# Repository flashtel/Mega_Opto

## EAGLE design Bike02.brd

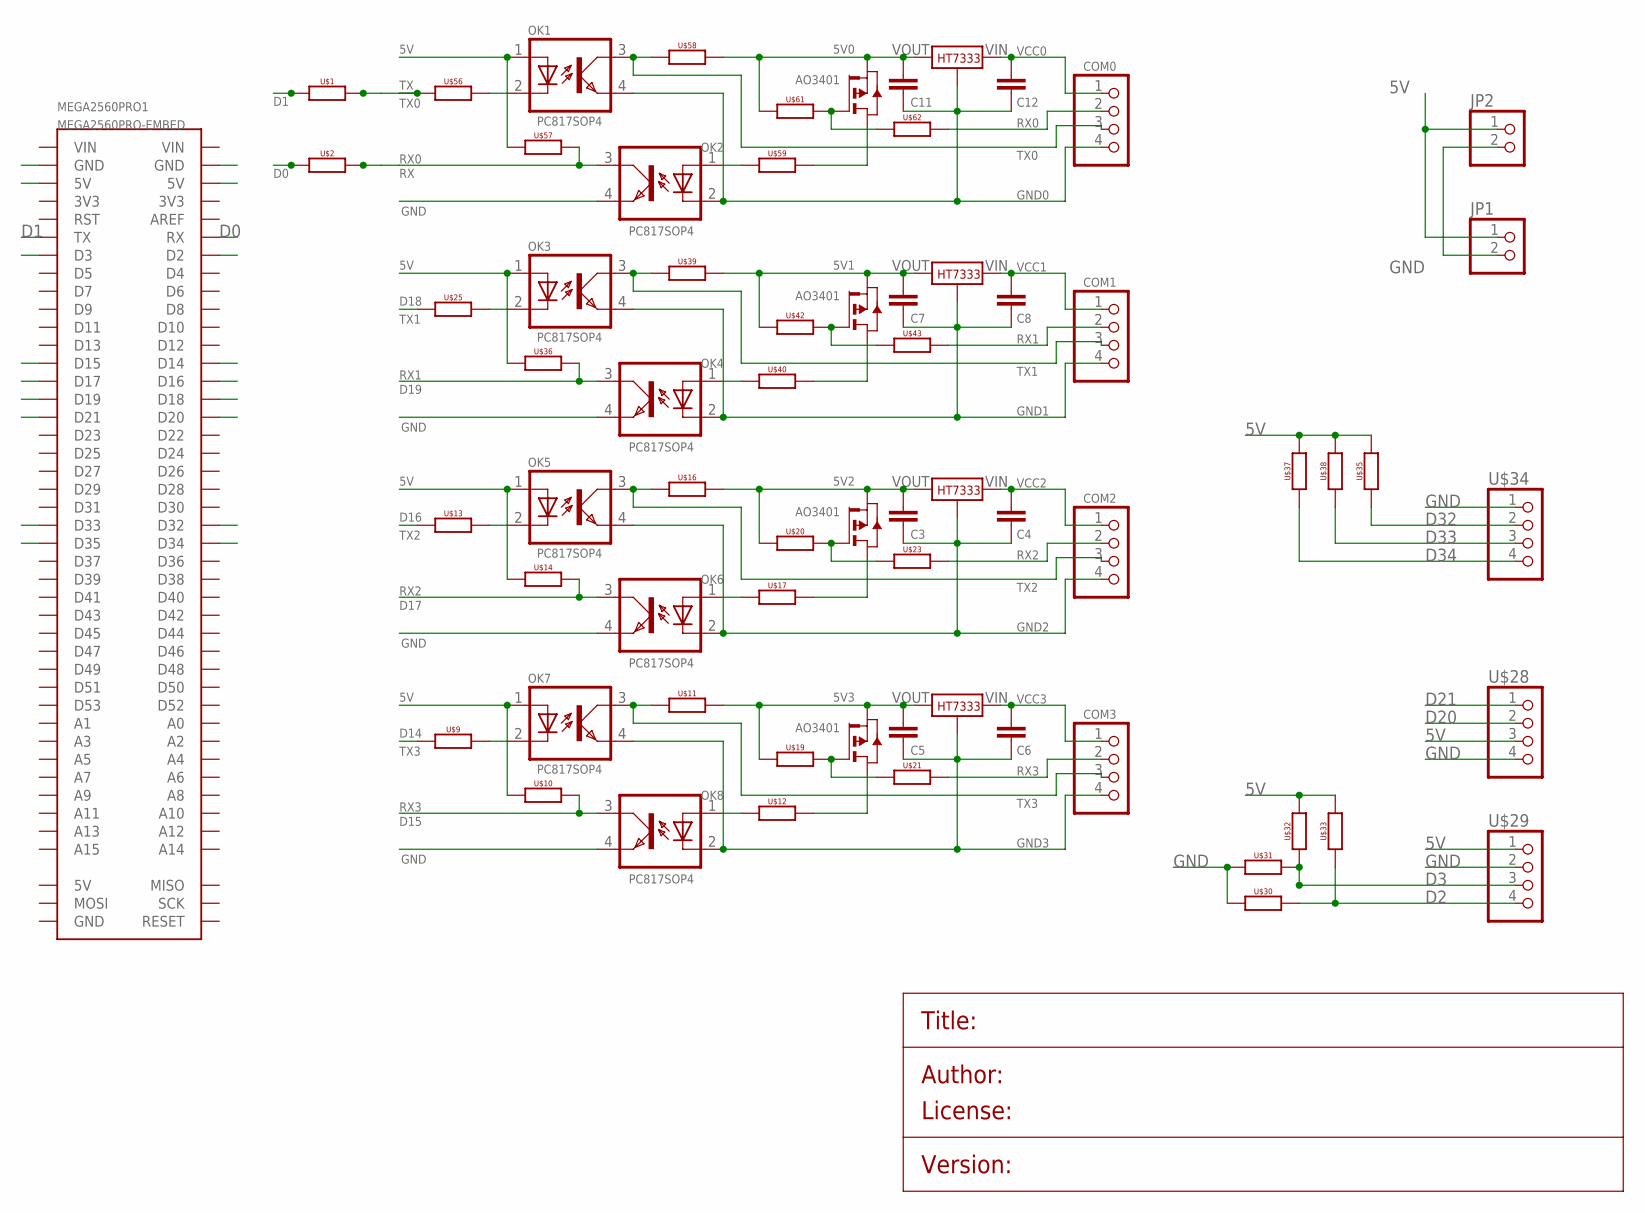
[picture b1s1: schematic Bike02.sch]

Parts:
C3, C4, C5, C6, C7, C8, C11, C12: CAPACITOR0805; 0805
COM0, COM1, COM2, COM3: PINHD-1X4_NO_SILK; 1X04_NO_SILK
JP1, JP2: PINHD-1X2-5_NO_SILK; 1X02-5_NO_SILK
MEGA2560PRO1: MEGA2560PRO-EMBED
OK1, OK2, OK3, OK4, OK5, OK6, OK7, OK8: PC817SOP4; SOP4-2.54
U$1, U$2, U$9, U$10, U$11, U$12, U$13, U$14, U$16, U$17, U$19, U$20, U$21, U$23, U$25, U$30, U$31, U$32, U$33, U$35, U$36, U$37, U$38, U$39, U$40, U$42, U$43, U$56, U$57, U$58, U$59, U$61, U$62: RESISTOR0805; 0805
U$15, U$18, U$41, U$60: AO3401; SOT23
U$22, U$24, U$44, U$63: HT7333; SOT89
U$28, U$29, U$34: PINHD-1X4_NO_SILK; 1X04_NO_SILK

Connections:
5V: JP1.1, JP2.1, MEGA2560PRO1.5V@1 (5V), MEGA2560PRO1.5V@2 (5V), OK1.1 (A), OK3.1 (A), OK5.1 (A), OK7.1 (A), U$10.1, U$14.1, U$28.3, U$29.1, U$32.2, U$33.2, U$35.2, U$36.1, U$37.2, U$38.2, U$57.1
5V0: C11.1, U$58.2, U$60.2 (S), U$61.1, U$63.VOUT
5V1: C7.1, U$39.2, U$41.2 (S), U$42.1, U$44.VOUT
5V2: C3.1, U$16.2, U$18.2 (S), U$20.1, U$24.VOUT
5V3: C5.1, U$11.2, U$15.2 (S), U$19.1, U$22.VOUT
D0: MEGA2560PRO1.RX, U$2.1
D1: MEGA2560PRO1.TX, U$1.1
D2: MEGA2560PRO1.D2, U$29.4, U$30.2, U$33.1
D3: MEGA2560PRO1.D3, U$29.3, U$31.2, U$32.1
D14: MEGA2560PRO1.D14, U$9.1
D15: MEGA2560PRO1.D15, OK8.3 (COL), U$10.2
D16: MEGA2560PRO1.D16, U$13.1
D17: MEGA2560PRO1.D17, OK6.3 (COL), U$14.2
D18: MEGA2560PRO1.D18, U$25.1
D19: MEGA2560PRO1.D19, OK4.3 (COL), U$36.2
D20: MEGA2560PRO1.D20, U$28.2
D21: MEGA2560PRO1.D21, U$28.1
D32: MEGA2560PRO1.D32, U$34.2, U$35.1
D33: MEGA2560PRO1.D33, U$34.3, U$38.1
D34: MEGA2560PRO1.D34, U$34.4, U$37.1
D35: MEGA2560PRO1.D35
GND: JP1.2, JP2.2, MEGA2560PRO1.GND@1 (GND), MEGA2560PRO1.GND@2 (GND), OK2.4 (EMIT), OK4.4 (EMIT), OK6.4 (EMIT), OK8.4 (EMIT), U$28.4, U$29.2, U$30.1, U$31.1, U$34.1
GND0: C11.2, C12.2, COM0.4, OK1.4 (EMIT), OK2.2 (C), U$63.GND
GND1: C7.2, C8.2, COM1.4, OK3.4 (EMIT), OK4.2 (C), U$44.GND
GND2: C3.2, C4.2, COM2.4, OK5.4 (EMIT), OK6.2 (C), U$24.GND
GND3: C5.2, C6.2, COM3.4, OK7.4 (EMIT), OK8.2 (C), U$22.GND
unnamed: OK7.2 (C), U$9.2
unnamed: OK5.2 (C), U$13.2
unnamed: OK6.1 (A), U$17.1
unnamed: OK8.1 (A), U$12.1
unnamed: U$12.2, U$15.3 (D)
unnamed: U$17.2, U$18.3 (D)
unnamed: U$18.1 (G), U$20.2, U$23.1
unnamed: U$15.1 (G), U$19.2, U$21.1
unnamed: OK3.2 (C), U$25.2
unnamed: OK4.1 (A), U$40.1
unnamed: U$40.2, U$41.3 (D)
unnamed: U$41.1 (G), U$42.2, U$43.1
unnamed: OK1.2 (C), U$56.2
unnamed: OK2.1 (A), U$59.1
unnamed: U$59.2, U$60.3 (D)
unnamed: U$60.1 (G), U$61.2, U$62.1
RX: OK2.3 (COL), U$2.2, U$57.2
RX0: COM0.2, U$62.2
RX1: COM1.2, U$43.2
RX2: COM2.2, U$23.2
RX3: COM3.2, U$21.2
TX: U$1.2, U$56.1
TX0: COM0.3, OK1.3 (COL), U$58.1
TX1: COM1.3, OK3.3 (COL), U$39.1
TX2: COM2.3, OK5.3 (COL), U$16.1
TX3: COM3.3, OK7.3 (COL), U$11.1
VCC0: C12.1, COM0.1, U$63.VIN
VCC1: C8.1, COM1.1, U$44.VIN
VCC2: C4.1, COM2.1, U$24.VIN
VCC3: C6.1, COM3.1, U$22.VIN

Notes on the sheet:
TX0
RX0
TX1
RX1
TX2
RX2
TX3
RX3

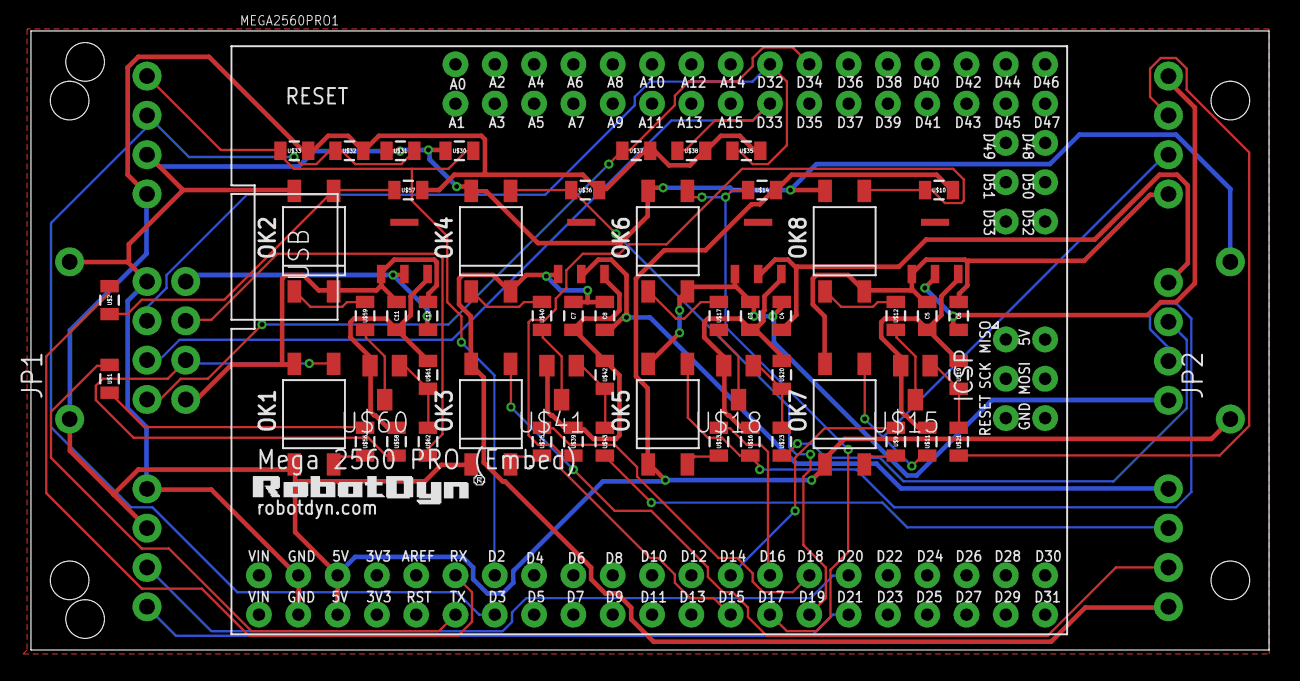
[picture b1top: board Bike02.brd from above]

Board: 2 copper layers, 80.0 x 40.0 mm, 67 parts (0 on the bottom side), 55 nets.

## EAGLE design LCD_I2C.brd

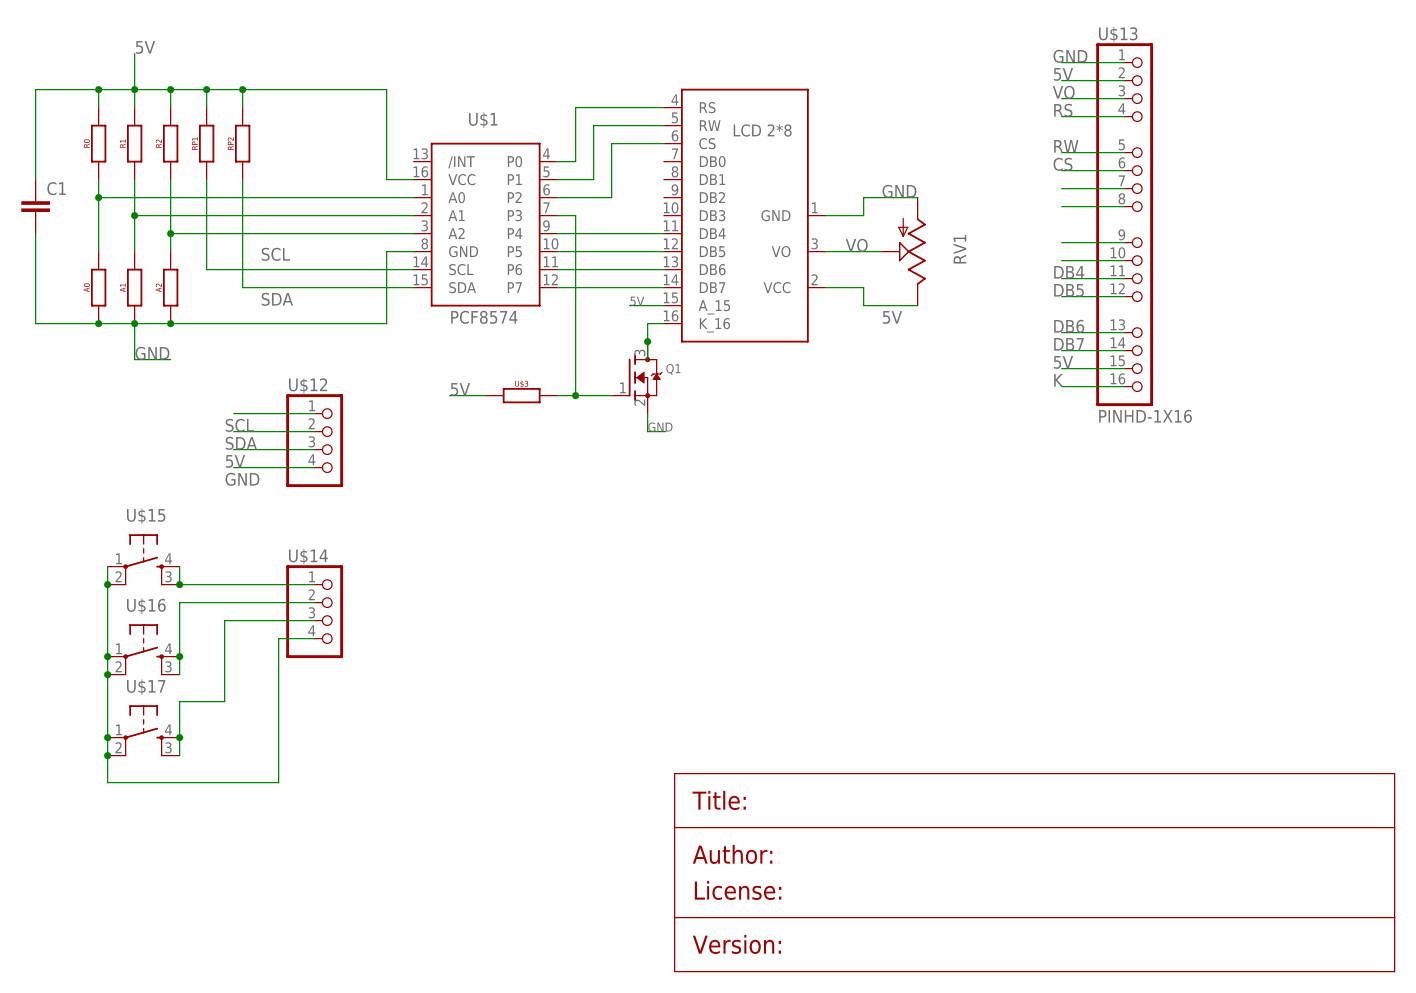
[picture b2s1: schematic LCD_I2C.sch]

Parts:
A0, A1, A2: RESISTOR0805; 0805
C1: CAPACITOR0805; 0805
Q1: MOSFET-N; SOT23-WIDE
R0, R1, R2: RESISTOR0805; 0805
RP1, RP2: RESISTOR0805; 0805
RV1: TRIM_POTB25P; B25P
U$1: PCF8574; SOIC16
U$2: LCD_28_A; LCD_2*8_A
U$3: RESISTOR0805; 0805
U$12, U$14: PINHD-1X4_NO_SILK; 1X04_NO_SILK
U$13: PINHD-1X16; 1X16_NO_SILK
U$15, U$16, U$17: TACTILE_BUTTON_SMD; TACTILE-BUTTON-SMD

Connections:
5V: C1.1, R0.2, R1.2, R2.2, RP1.2, RP2.2, RV1.E, U$1.16 (VCC), U$2.2 (VCC), U$2.15 (A_15), U$3.1, U$12.3, U$13.2, U$13.15
CS: U$1.6 (P2), U$2.6 (CS), U$13.6
DB4: U$1.9 (P4), U$2.11 (DB4), U$13.11
DB5: U$1.10 (P5), U$2.12 (DB5), U$13.12
DB6: U$1.11 (P6), U$2.13 (DB6), U$13.13
DB7: U$1.12 (P7), U$2.14 (DB7), U$13.14
GND: A0.1, A1.1, A2.1, C1.2, Q1.2 (S), RV1.A, U$1.8 (GND), U$2.1 (GND), U$12.4, U$13.1
K: Q1.3 (D), U$2.16 (K_16), U$13.16
unnamed: U$14.4, U$15.1 (SWA1), U$15.2 (SWB1), U$16.1 (SWA1), U$16.2 (SWB1), U$17.1 (SWA1), U$17.2 (SWB1)
unnamed: U$14.1, U$15.3 (SWB2), U$15.4 (SWA2)
unnamed: U$14.2, U$16.3 (SWB2), U$16.4 (SWA2)
unnamed: A0.2, R0.1, U$1.1 (A0)
unnamed: U$14.3, U$17.3 (SWB2), U$17.4 (SWA2)
unnamed: Q1.1 (G), U$1.7 (P3), U$3.2
unnamed: A1.2, R1.1, U$1.2 (A1)
unnamed: A2.2, R2.1, U$1.3 (A2)
RS: U$1.4 (P0), U$2.4 (RS), U$13.4
RW: U$1.5 (P1), U$2.5 (RW), U$13.5
SCL: RP1.1, U$1.14 (SCL), U$12.1
SDA: RP2.1, U$1.15 (SDA), U$12.2
VO: RV1.S, U$2.3 (VO), U$13.3

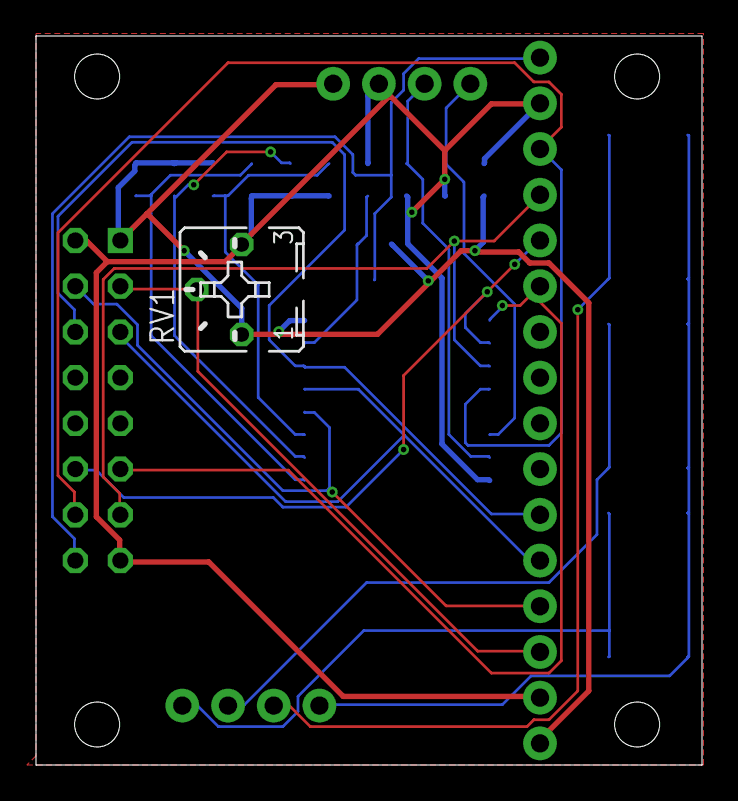
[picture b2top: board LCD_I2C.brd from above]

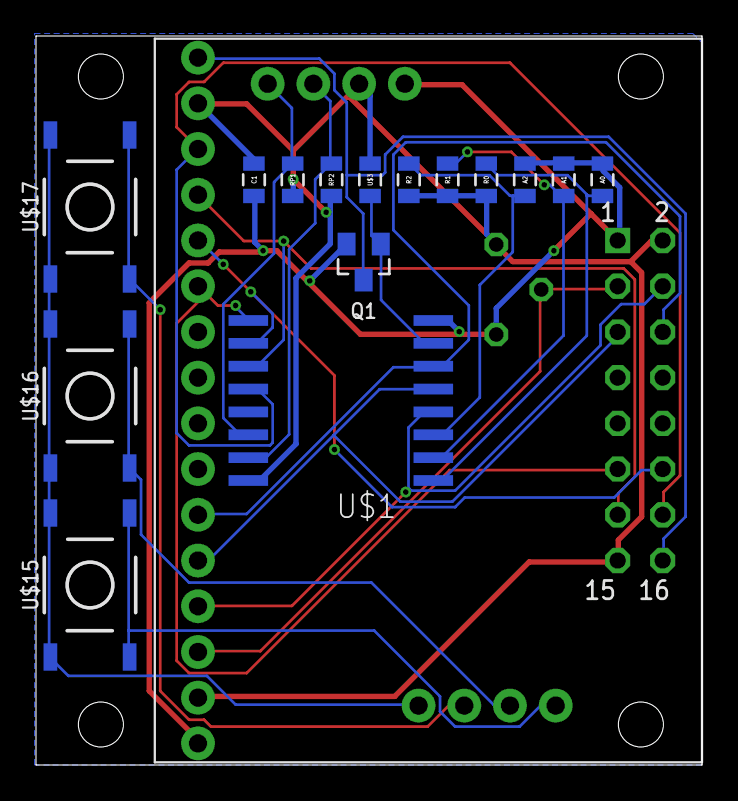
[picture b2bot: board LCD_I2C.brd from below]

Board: 2 copper layers, 37.0 x 40.5 mm, 20 parts (16 on the bottom side), 21 nets.

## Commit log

2020-01-01 Create
